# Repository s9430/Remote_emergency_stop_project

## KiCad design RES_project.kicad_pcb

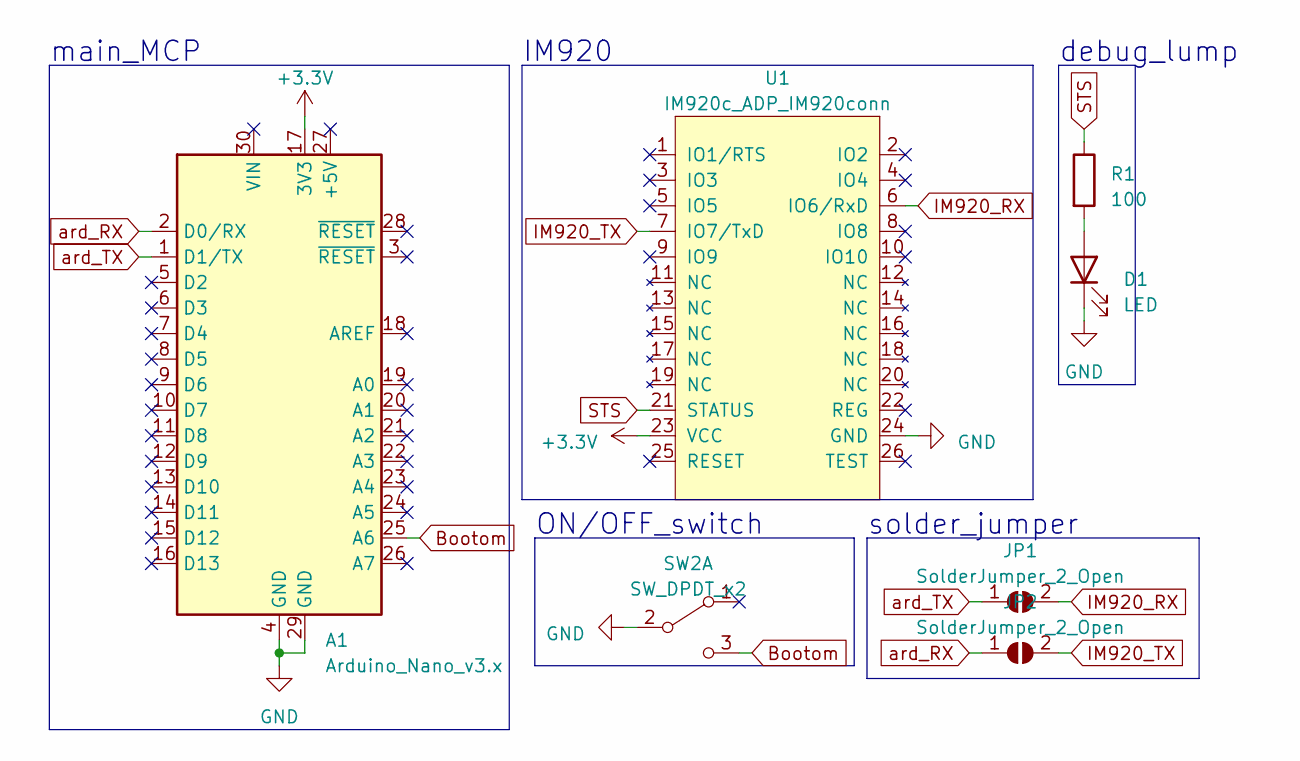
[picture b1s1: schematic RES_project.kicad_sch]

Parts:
A1: Arduino_Nano_v3.x; Arduino_Nano
D1: LED; LED_0603_1608Metric
JP1, JP2: SolderJumper_2_Open; PinHeader_1x02_P2.54mm_Vertical
R1: 100; R_0603_1608Metric
SW2: SW_DPDT_x2; Switch_SMD_BIG
U1: IM920c_ADP_IM920conn; IM920(IM920c_ADP)

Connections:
+3.3V: A1.17 (3V3), U1.23 (VCC)
Bootom: A1.25 (A6), SW2.3 (C)
GND: A1.4 (GND), A1.29 (GND), D1.1 (K), SW2.2 (B), U1.24 (GND)
IM920_RX: JP1.2 (B), U1.6 (IO6/RxD)
IM920_TX: JP2.2 (B), U1.7 (IO7/TxD)
unnamed: D1.2 (A), R1.2
STS: R1.1, U1.21 (STATUS)
ard_RX: A1.2 (D0/RX), JP2.1 (A)
ard_TX: A1.1 (D1/TX), JP1.1 (A)

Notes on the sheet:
IM920
main_MCP
ON/OFF_switch
debug_lump
solder_jumper

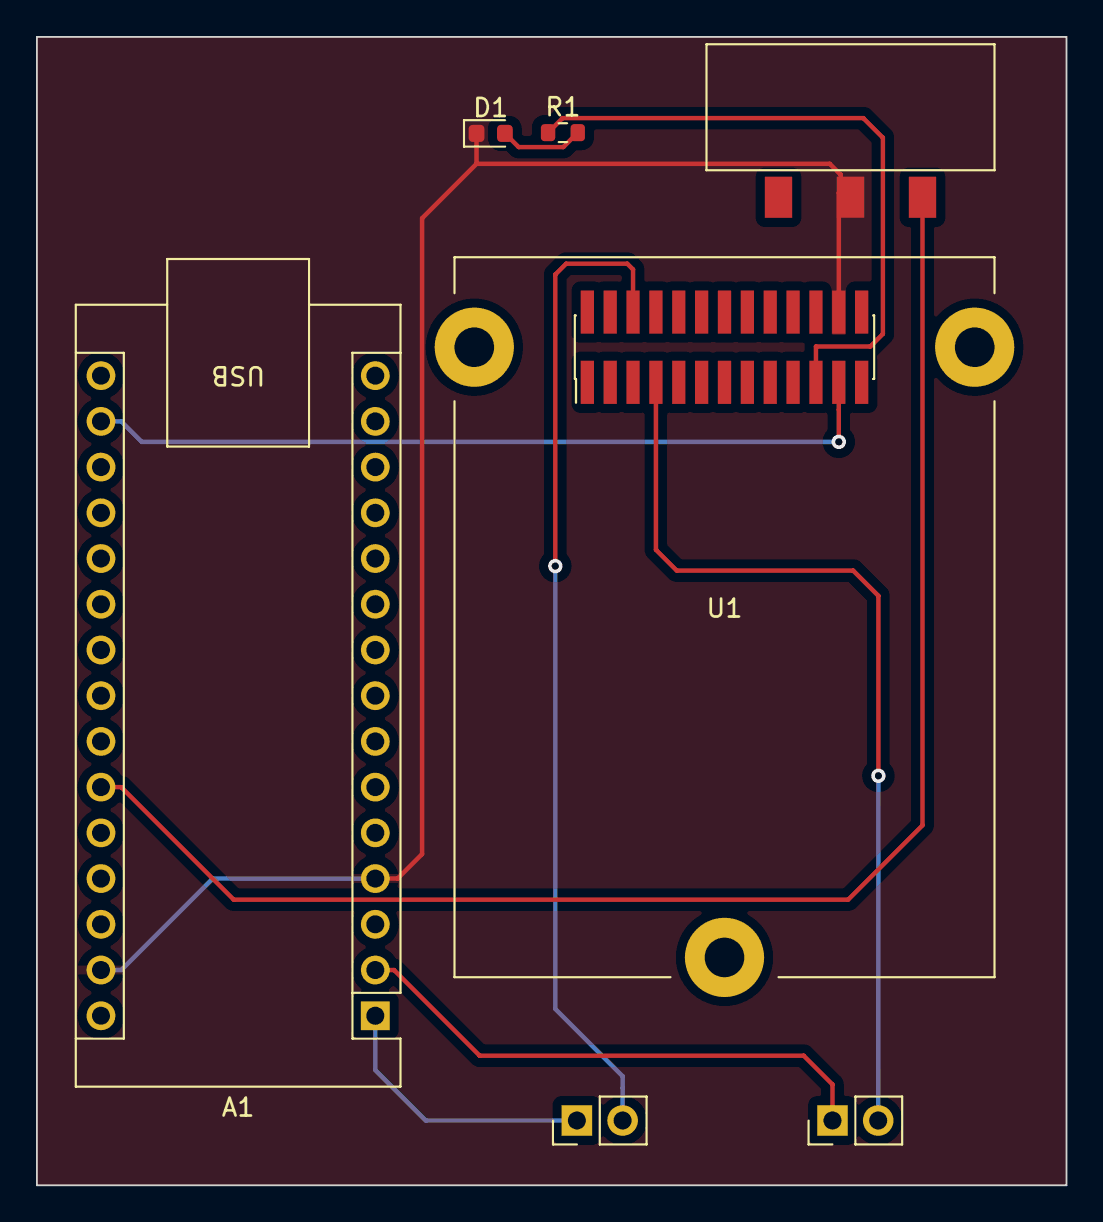
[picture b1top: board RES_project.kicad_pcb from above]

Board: 2 copper layers, 57.2 x 63.8 mm, 7 parts (0 on the bottom side), 9 nets.
